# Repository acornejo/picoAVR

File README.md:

# [PicoAVR](http://acornejo.github.io/picoAVR)

[PicoAVR](http://acornejo.github.io/picoAVR) is an open source AVR
development board which aims to a minimalistic but fully functional
alternative to Arduino.
The PicoAVR board measures less than 1 square inch, and for less than 10$ you can buy all the components to build your own.

The PicoAVR can be powered and programmed through a standard MicroUSB
connector, the same connector used by android phones and tablets.
PicoAVR uses the [V-USB](http://www.obdev.at/products/vusb/index.html)
software implementation of the USB stack, and when connected to your
computer can easily be programmed to emulate a keyboard,
mouse or any other HID device.

The PicoAVR board is similar in capabilities to the [Arduino
UNO](http://arduino.cc/en/Main/ArduinoBoardUno), [Arduino
Micro](http://arduino.cc/en/Main/arduinoBoardMicro) or the [Arduino
Leonardo](http://arduino.cc/en/Main/arduinoBoardLeonardo), but by using
an atmega328p and V-USB instead of an FTDI chip or an atmega328u4 the
number of components and the cost of the PicoAVR is significantly
reduced.

Since PicoAVR uses the same
[protocol](http://www.obdev.at/products/vusb/usbasploader.html) as the
[usbasp](www.fischl.de/usbasp/) for programming, it is supported by
the latest versions of avrdude. As a result both 
Atmel Studio 6 or the Arduino Software can be used as complete
development environments for the PicoAVR. However, you are not
constrained to these, and you can easily develop for the PicoAVR using
avr-gcc, avrdude and the editor of your choice.

In its default configuration the PicoAVR runs at 12 Mhz and operates at
3.3 V, which makes it easy to interface to the newer 3.3 V devices without
requiring a level shifter.

## PicoAVR may be interesting to you if...

* You are already developing hardware projects using an Arduino, but you
would prefer to build your own hardware.
* You want to get started with AVR microcontrollers, but don't want to
spend 25$ on an Arduino UNO or an Arduino Micro.
* You want an AVR development board which has a standard 6-pin ICSP
connector and can be used as an ICSP programmer for other
microcontrollers.
* You want to create a board of your own using an AVR microcontroller
and you are looking for a simple reference design.

## Build Your Own

You can buy the components to build your own for less than 10$ per board.

Moreover, keep in mind that due to economies of scale, building 100 or
1000 PicoAVR's is significantly cheaper per unit than building a single
board.

The only equipment required to build your own PicoAVR is a soldering
iron and an ICSP programmer to flash the bootloader (more on that below).

### BOM

|Part  | Description               | Package      | DigiKey Part #       | Price ($) |
|------|---------------------------|--------------|----------------------|-----------|
|C1,C2 | 4.7uF Capacitor           | 402          | 1276-1056-1-ND       | 0.23 x 2  |
|C3,C4 | 22pF  Capacitor           | 402          | 1276-1681-1-ND       | 0.1 x 2   |
|C5,C6 | 0.1uF Capacitor           | 402          | 1276-1443-1-ND       | 0.1 x 2   |
|R1,R2 | 68 Ohm Resistor           | 402          | RMCF0402JT68R0CT-ND  | 0.02 x 2  |
|R3    | 1.5k Ohm Resistor         | 402          | RMCF0402JT1K50CT-ND  | 0.02 x 1  |
|R4    | 10k Ohm Resistor          | 402          | RMCF0402JT10K0CT-ND  | 0.02 x 1  |
|R5    | 220 Ohm Resistor          | 402          | RMCF0402JT220RCT-ND  | 0.02 x 1  |
|Q1    | 12 Mhz Crystal            | 3.2 x 2.5mm  | 887-2355-1-ND        | 0.71 x 1  |
|U1    | Atmega328p                | TQFP-32      | ATMEGA328P-AU-ND     | 3.61 x 1  |
|IC1   | MCP1700 Voltage Regulator | SOT23        | MCP1700T3302ETTCT-ND | 0.44 x 1  |
|X1    | MicroUSB Connector        | USB-MICRO    | 609-4613-1-ND        | 0.46 x 1  |
|SW1   | Tactile Switch            | 3mm x 4mm    | CKN10502CT-ND        | 0.28 x 1  |

The total comes to less than 6.5$ per board. Digikey offers educational and
bulk discounts.

### PCB

You can get 3 PCB's from [oshpark.com](https://oshpark.com/shared_projects/4zQfKzvO) for only 4.95$
including shipping. That is less than 2$ per PicoAVR board! Click [here](https://oshpark.com/shared_projects/4zQfKzvO) to order your own. 

The eagle board files are available in the
[repository](https://github.com/acornejo/picoAVR/tree/master/hardware).

Below is a rendering of the top and bottom of the PCB.

### Flashing the Bootloader
To get the PicoAVR usbasp-based bootloader flashed into the AVR chip you will
need either: a dedicated [ICSP
programmer](http://store.atmel.com/PartDetail.aspx?q=p:10500054#tc:description),
an [Arduino](http://arduino.cc/en/Tutorial/ArduinoISP) and jumper
cables, or an already functioning PicoAVR.

The PicoAVR provides a standard 6-pin ICSP connector that can be used to
either flash the bootloader into the board (by closing the self-program
jumper), or to act as an ICSP programmer to reprogram any other
AVR board (including another PicoAVR or an Arduino) using a standard
6-pin ICSP connector.

## License

[MIT License](http://opensource.org/licenses/MIT)

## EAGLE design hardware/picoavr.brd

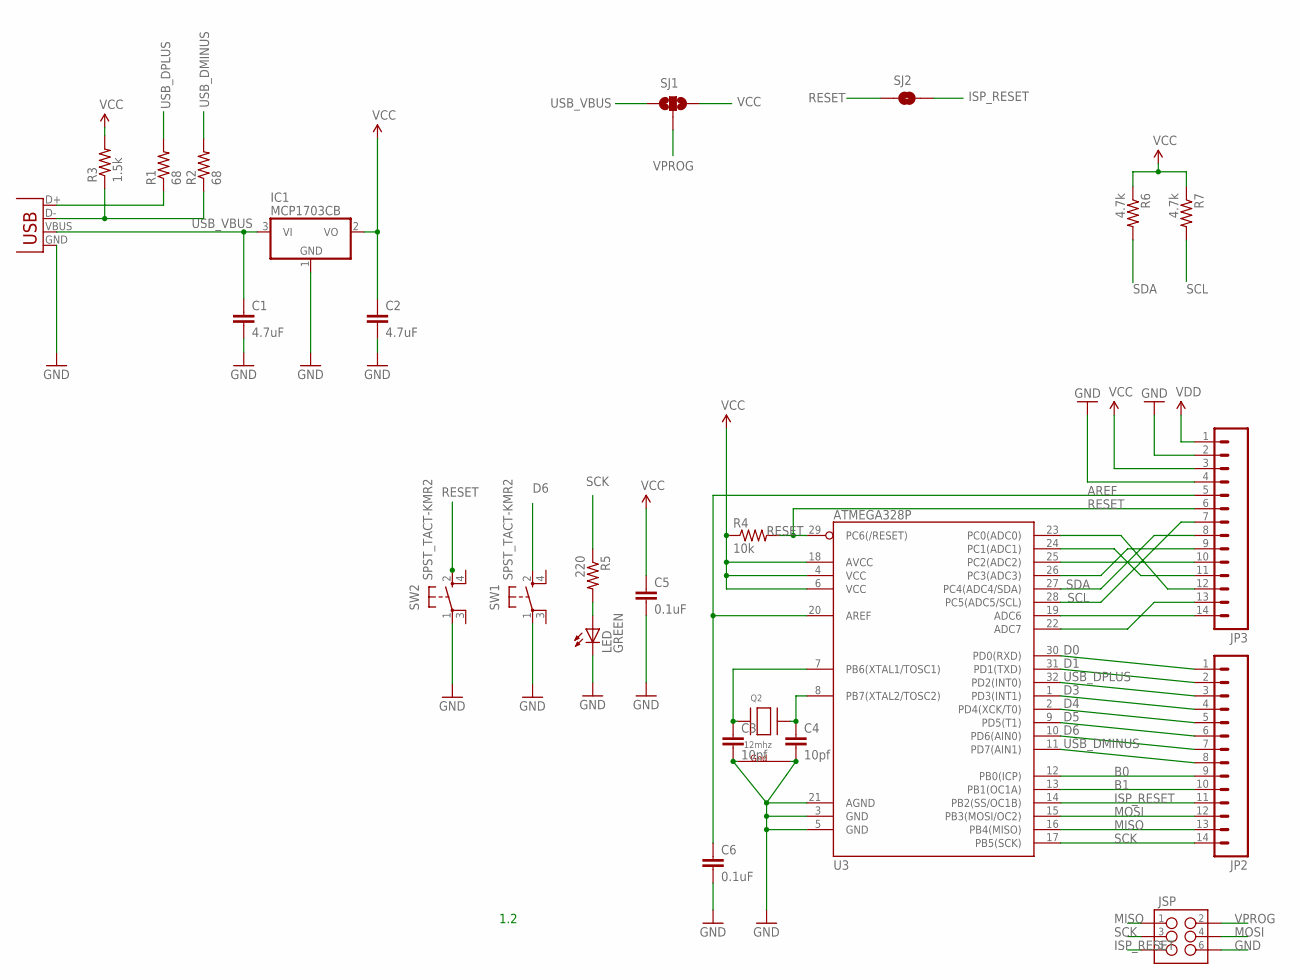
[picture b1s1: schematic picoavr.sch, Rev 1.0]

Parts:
C1, C2: 4.7uF; 0402-CAP
C3, C4: 10pf; 0402-CAP
C5, C6: 0.1uF; 0402-CAP
IC1: MCP1703CB; SOT23
JP2, JP3: M14LOCK; 1X14_LOCK
JSP: ICSP; 2X3-NS
LED: GREEN; LED-0603
Q2: 12mhz; NX3225
R1, R2: 68; R0402
R3: 1.5k; R0402
R4: 10k; R0402
R5: 220; 0402-RES
R6, R7: 4.7k; 0402-RES
SJ1: SJ1; SJ_3
SJ2: SOLDERJUMPERNO; SJ_2S-NO
SW1, SW2: SPST_TACT-KMR2; KMR2
U3: ATMEGA328P; TQFP32-08
X1: Micro USB; USB-MICROB

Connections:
A0: JP3.12, U3.23 (PC0(ADC0))
A1: JP3.11, U3.24 (PC1(ADC1))
A2: JP3.10, U3.25 (PC2(ADC2))
A3: JP3.9, U3.26 (PC3(ADC3))
A6: JP3.14, U3.19 (ADC6)
A7: JP3.13, U3.22 (ADC7)
AREF: C6.1, JP3.5, U3.20 (AREF)
B0: JP2.9, U3.12 (PB0(ICP))
B1: JP2.10, U3.13 (PB1(OC1A))
D0: JP2.1, U3.30 (PD0(RXD))
D1: JP2.2, U3.31 (PD1(TXD))
D3: JP2.4, U3.1 (PD3(INT1))
D4: JP2.5, U3.2 (PD4(XCK/T0))
D5: JP2.6, U3.9 (PD5(T1))
D6: JP2.7, SW1.2 (S), U3.10 (PD6(AIN0))
GND: C1.2, C2.2, C3.2, C4.2, C5.2, C6.2, IC1.1 (GND), JP3.2, JP3.4, JSP.6, LED.C, Q2.2 (G2), Q2.4 (G1), SW1.1, SW2.1, U3.3 (GND), U3.5 (GND), U3.21 (AGND), X1.GND
ISP_RESET: JP2.11, JSP.5, SJ2.2, U3.14 (PB2(SS/OC1B))
MISO: JP2.13, JSP.1, U3.16 (PB4(MISO))
MOSI: JP2.12, JSP.4, U3.15 (PB3(MOSI/OC2))
unnamed: R1.1, X1.D+
unnamed: R2.1, R3.1, X1.D-
unnamed: C4.1, Q2.3 (X2), U3.8 (PB7(XTAL2/TOSC2))
unnamed: C3.1, Q2.1 (X1), U3.7 (PB6(XTAL1/TOSC1))
unnamed: LED.A, R5.2
RESET: JP3.6, R4.2, SJ2.1, SW2.2 (S), U3.29 (PC6(/RESET))
SCK: JP2.14, JSP.3, R5.1, U3.17 (PB5(SCK))
SCL: JP3.7, R7.2, U3.28 (PC5(ADC5/SCL))
SDA: JP3.8, R6.2, U3.27 (PC4(ADC4/SDA))
USB_DMINUS: JP2.8, R2.2, U3.11 (PD7(AIN1))
USB_DPLUS: JP2.3, R1.2, U3.32 (PD2(INT0))
USB_VBUS: C1.1, IC1.3 (VI), JP3.1, SJ1.1, X1.VBUS
VCC: C2.1, C5.1, IC1.2 (VO), JP3.3, R3.2, R4.1, R6.1, R7.1, SJ1.3, U3.4 (VCC), U3.6 (VCC), U3.18 (AVCC)
VPROG: JSP.2, SJ1.2

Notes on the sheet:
1.2

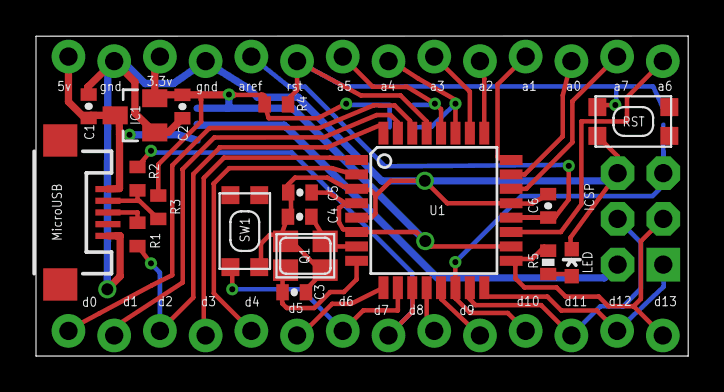
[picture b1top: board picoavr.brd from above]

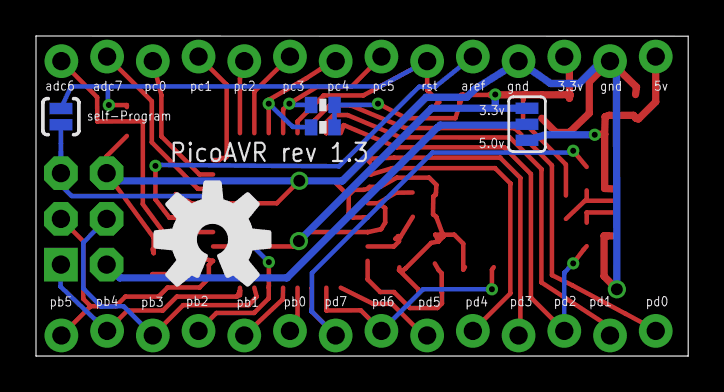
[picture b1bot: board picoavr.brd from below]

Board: 2 copper layers, 36.2 x 17.8 mm, 25 parts (4 on the bottom side), 33 nets.

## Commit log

2014-05-18 first
2014-05-18 fix project file
2014-05-18 update project
2014-05-18 add export scripts
2014-05-18 add composite script
2014-05-19 fix drill circles
2014-05-19 continue with composite
2014-05-19 moved file around
2014-05-19 fix use undo instead of remove.
2014-05-19 fix composite
2014-05-20 fix some traces
2014-05-20 finish composite
2014-05-20 add export script
2014-05-20 change names
2014-05-26 added bootloader
2014-05-26 clean up code a bit (at the expense of size)
2014-05-26 add usbasp programmer
2014-05-26 add usbdrv v-usb
2014-05-26 add blinky example
2014-05-26 simplified makefiles
2014-05-26 change address
2014-05-28 change directory structure
2014-05-28 update makefile
2014-05-28 update bootloader makefile
2014-05-30 configured jumper port
2014-06-02 add missing labels
2014-06-04 first page commit
2014-06-04 add images
2014-06-04 add solo
2014-06-04 change link
2014-06-04 updated docs
2014-06-04 add image
2014-06-04 add second image
2014-06-04 update images
2014-06-04 added extensions for tables
2014-06-04 add tables
2014-06-04 widen container
2014-06-04 updated container
2014-06-04 add readme
2014-06-04 fixed images
2014-06-05 change to use readme
2014-06-05 add header
2014-06-05 remove double header
2014-06-05 update docs
2014-06-05 add photo
2014-06-05 update image
2014-06-05 changed button placement
2014-06-05 change led placement
2014-06-05 remove readme from gh-pages
2014-06-05 new hardware revision
2014-06-05 moved labels
2014-06-05 fix pin spacing
2014-06-05 tweaked dimensions
2014-06-05 add size to description
2014-06-11 change pc7/pc6 label to adc7/adc6
2014-06-23 minor trace tweaks
2014-06-25 add optional reset button
2014-06-25 move reset for silk screen
2014-07-10 update device in bootloader
2014-07-10 fix typo in readme
2014-07-10 add new photo
2014-07-10 update board file

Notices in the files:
parts and their libraries:
SparkFun-DigitalIC: Licensing: Creative Commons ShareAlike 4.0 International - https://creativecommons.org/licenses/by-sa/4.0
